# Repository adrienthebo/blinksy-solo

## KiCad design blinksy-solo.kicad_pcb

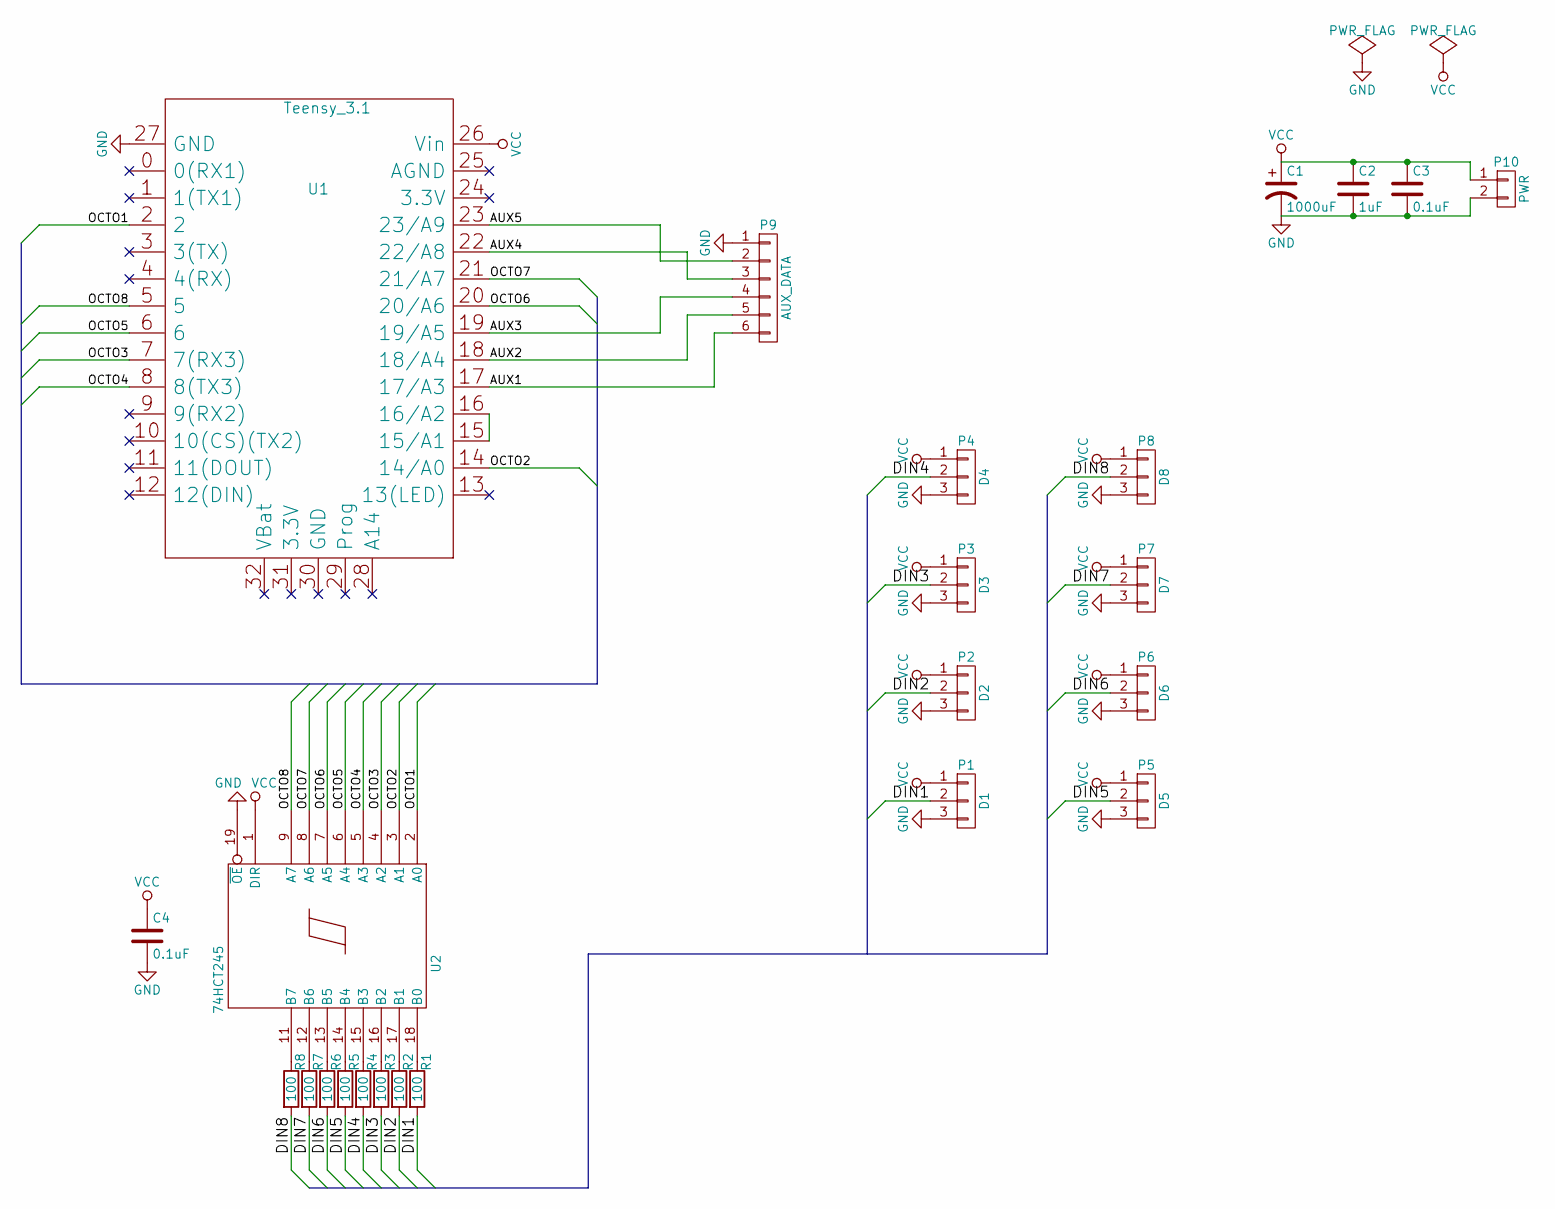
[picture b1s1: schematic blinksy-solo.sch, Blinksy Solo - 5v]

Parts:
C1: 1000uF; C_Radial_D13_L25_P5
C2: 1uF; C_Disc_D6_P5
C3, C4: 0.1uF; C_Disc_D6_P5
P1: D1; Pin_Header_Straight_1x03
P2: D2; Pin_Header_Straight_1x03
P3: D3; Pin_Header_Straight_1x03
P4: D4; Pin_Header_Straight_1x03
P5: D5; Pin_Header_Straight_1x03
P6: D6; Pin_Header_Straight_1x03
P7: D7; Pin_Header_Straight_1x03
P8: D8; Pin_Header_Straight_1x03
P9: AUX_DATA; Pin_Header_Straight_1x06
P10: PWR; Pin_Header_Straight_1x02
R1, R2, R3, R4, R5, R6, R7, R8: 100; Resistor_Horizontal_RM10mm
U1: Teensy_3.1; Teensy-3.1
U2: 74HCT245; DIP-20_W7.62mm

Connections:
/AUX1: P9.6, U1.17 (17/A3)
/AUX2: P9.5, U1.18 (18/A4)
/AUX3: P9.4, U1.19 (19/A5)
/AUX4: P9.3, U1.22 (22/A8)
/AUX5: P9.2, U1.23 (23/A9)
/DIN1: P1.2, R1.2
/DIN2: P2.2, R2.2
/DIN3: P3.2, R3.2
/DIN4: P4.2, R4.2
/DIN5: P5.2, R5.2
/DIN6: P6.2, R6.2
/DIN7: P7.2, R7.2
/DIN8: P8.2, R8.2
/OCTO1: U1.2, U2.2 (A0)
/OCTO2: U1.14 (14/A0), U2.3 (A1)
/OCTO3: U1.7 (7(RX3)), U2.4 (A2)
/OCTO4: U1.8 (8(TX3)), U2.5 (A3)
/OCTO5: U1.6, U2.6 (A4)
/OCTO6: U1.20 (20/A6), U2.7 (A5)
/OCTO7: U1.21 (21/A7), U2.8 (A6)
/OCTO8: U1.5, U2.9 (A7)
GND: C1.2, C2.2, C3.2, C4.2, P1.3, P2.3, P3.3, P4.3, P5.3, P6.3, P7.3, P8.3, P9.1, P10.2, U1.27 (GND), U2.10 (GND), U2.19 (~OE)
unnamed: R1.1, U2.18 (B0)
unnamed: R2.1, U2.17 (B1)
unnamed: R3.1, U2.16 (B2)
unnamed: R4.1, U2.15 (B3)
unnamed: R5.1, U2.14 (B4)
unnamed: R6.1, U2.13 (B5)
unnamed: R7.1, U2.12 (B6)
unnamed: R8.1, U2.11 (B7)
unnamed: U1.15 (15/A1), U1.16 (16/A2)
VCC: C1.1, C2.1, C3.1, C4.1, P1.1, P2.1, P3.1, P4.1, P5.1, P6.1, P7.1, P8.1, P10.1, U1.26 (Vin), U2.1 (DIR), U2.20 (VCC)

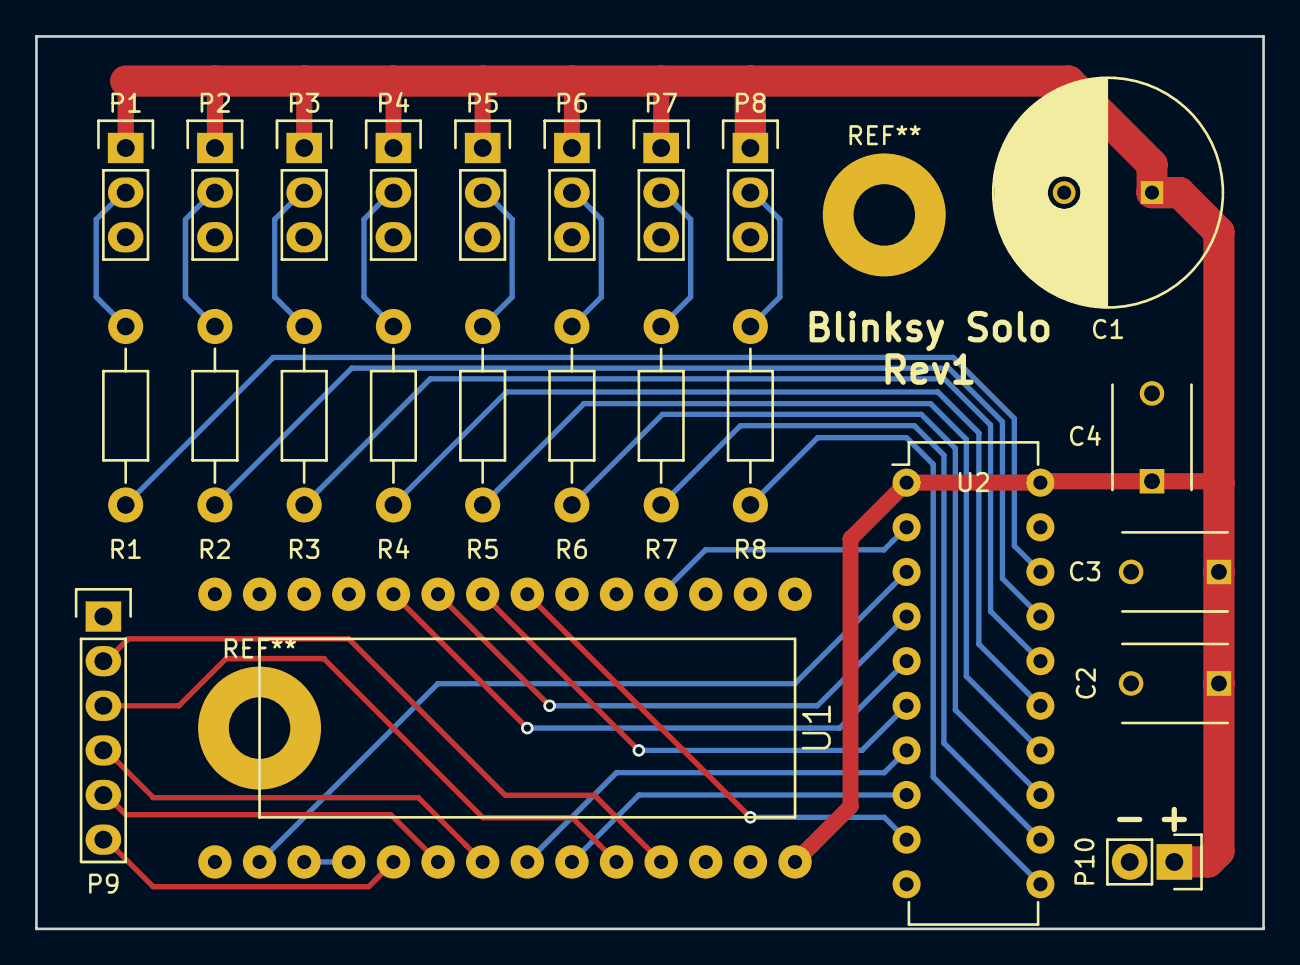
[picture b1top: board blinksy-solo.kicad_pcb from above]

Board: 2 copper layers, 69.8 x 50.8 mm, 24 parts (0 on the bottom side), 32 nets.

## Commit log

2016-04-22 Initial commit. All the things.
2016-04-22 Ignore backups and autosaves
2016-04-22 redraw ground ground plane closer to edge
2016-04-22 Expand ground plane more, fix disconnected pins
2016-04-24 Minor layout touchups
2016-04-24 Ignore gerber exports
2016-04-28 Add footprint for 3mm screw holes
2016-04-28 Finalize rev1
2016-05-12 Add VERSIONS file
2016-05-12 Bump rev to 2, drop issue date
2016-05-23 Update checklist
2016-11-13 VERSIONS: note ground pins for AUX
